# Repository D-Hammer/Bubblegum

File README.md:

# Bubblegum
## Integrated control board

### Scope: 
- Interface with an RC receiver
  - Sbus is priority
  - Other variants will be created later
- Control drive motors
  - 2 motors priority
  - 4 motors later to allow use for Mecanum, etc.
- Control weapon motor
- IMU/PID drive to make up for my lack of driving skill
- Remote adjustable expo, user selectable mixing, sense and remix for inverted driving, remote switch for PID

### To Do
- Test and tune on various drive topologies
- Branch HW and FW to interface w/ standard pwm receivers

# Changelog
## Hardware

### V1.30
- Reduced footprint to 0.94"x0.94"
- Through holes for outputs are now pads to allow for a more compact profile
- 0.8mm FR4, 2oz Cu
- 0.050" pitch programming header

### V1.20
- IMU integrated into control board.  
- 3.3v power system added
- Decreased current capacity on 5V supply to free up board space
- 0.8mm FR4, 2oz Cu

### V1.10
- Increased power input hole diameters

### V1.01
- Rerouted weapon pwm signal to different GPIO
- Added versioning and logo on back silk
- 1.5mm FR4, 1oz Cu

### V1.00
- Prototype
- 0.8mm FR4, 2oz Cu

## Firmware

### 2/6/18
- Minor tweaks to main loop
- Throttle scaling factor added to PID to improve low throttle stability and high throttle tracking
- New boot sequence to communicate with PID tuner
- Library change from SoftwareSerial to NeoSWSerial
- PID Tuner: New, alpha release, programming functions reliably, reading is buggy

### 11/20/17
- Added weapon output to DS branch (servo lib implementation)
- Update PWM branch with DS branch improvements
- New PID gains: P1.8 I0.02 D0.005

### 11/17/17
- Filtered the inversion sensing
- added deadband to PID to stop zero throttle flutter
- PID correction now proportional to throttle input [0.5 + abs(spd)]
- Tuned gains. Settled on P1.2 I0.02 D0.05

### 11/15/17
- Added deadband to drive inputs
- Increased data inclusivity on gyro calibration
- Fixed expo scaling issue
- Fixed sign of gyroOffset in PID
- DShot center is 1048 in 3D mode, NOT 1047 :/

### 11/14/17 
- Added alternate FW for DShot implementation
- dshot fiddlings file uses UART and requires inverter (untested) (DShot150)
- bit banging like an animal is addressable on port D and functional (DShot600)
- New FW syncs ESC update with PID loop and increases frequency from 140 Hz to ~1KHz
- All the standard anti-jitter, digital, checksum goodness you've come to expect from DShot!

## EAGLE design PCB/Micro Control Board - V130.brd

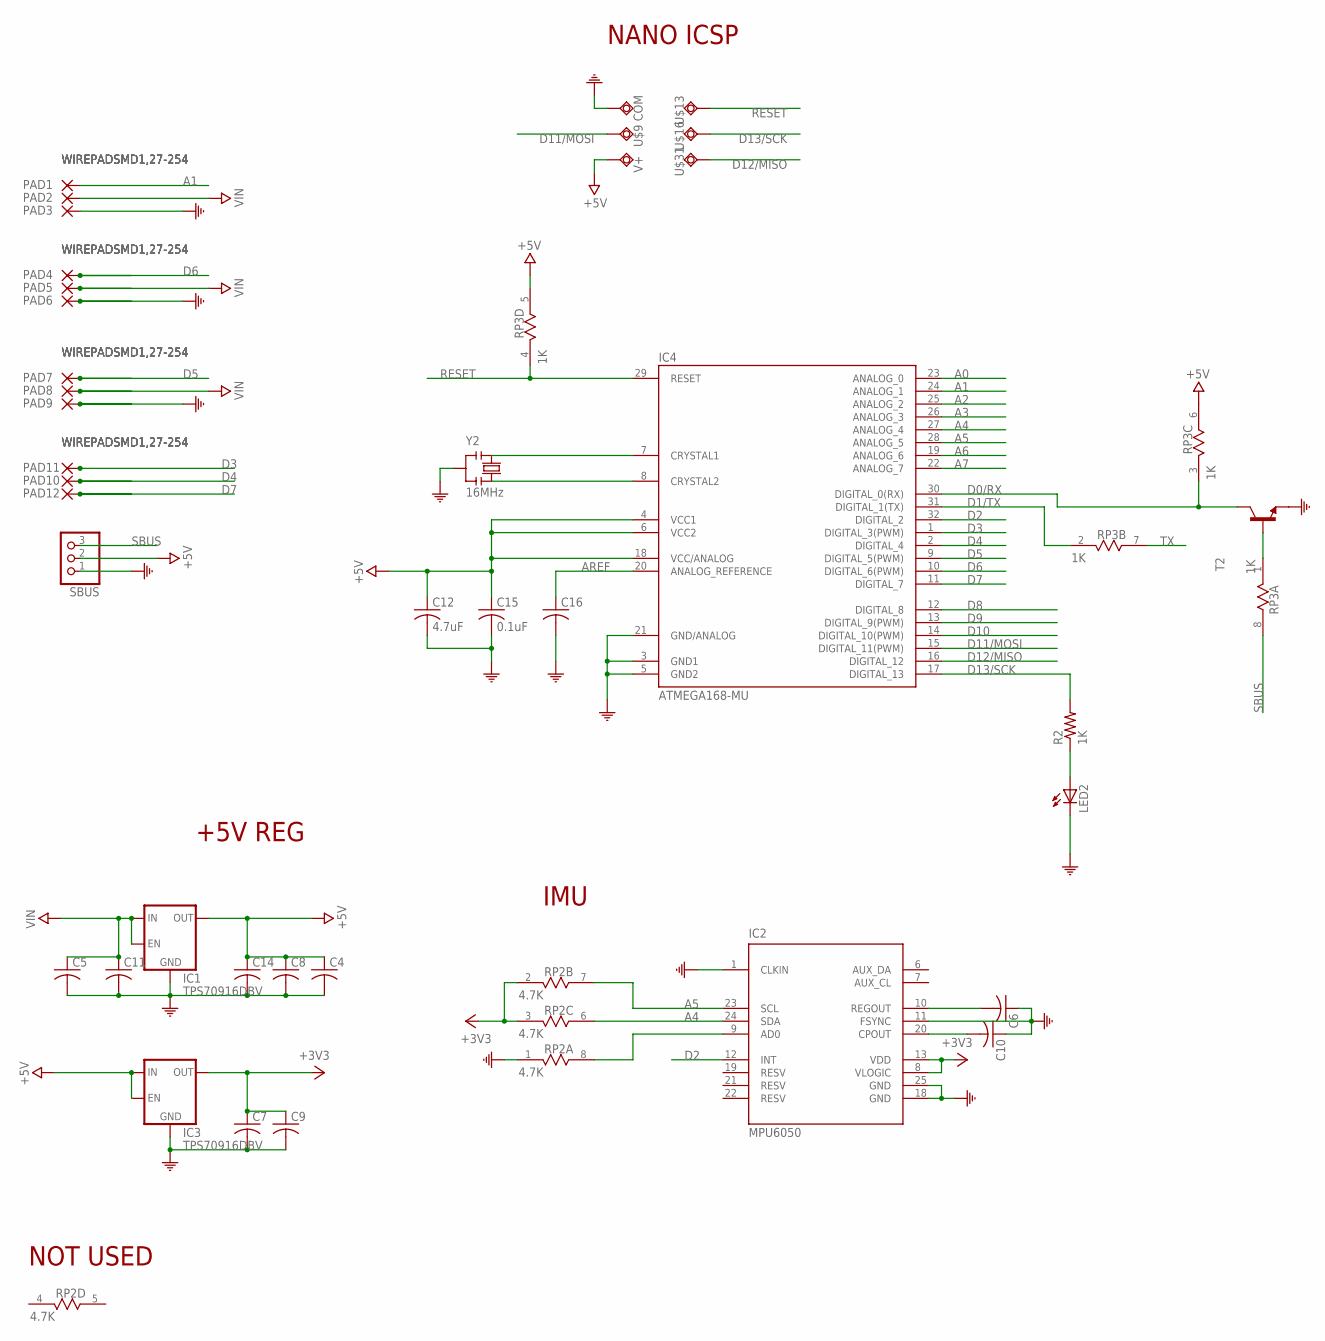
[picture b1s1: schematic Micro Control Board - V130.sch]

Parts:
C4, C5, C6, C7, C8, C9, C10, C11, C14, C16: C-USC0402; C0402
C12: 4.7uF; C0402
C15: 0.1uF; C0402
COM: 0.7MM-THRU; 0.65MM-THRU
IC1, IC3: TPS70916DBV; SOT23-5
IC2: MPU6050; QFN50P400X400X95-25T265X275N
IC4: ATMEGA168-MU; MLF32
LED2: LEDCHIP-LED0603; CHIP-LED0603
PAD1, PAD2, PAD3, PAD4, PAD5, PAD6, PAD7, PAD8, PAD9, PAD10, PAD11, PAD12: WIREPADSMD1,27-254; SMD1,27-2,54
R2: 1K; R0402
RP2: 4.7K; RES4NT
RP3: 1K; RES4NT
SBUS: PINHD-1X3; 1X03
T2: MMBT3904LT1-NPN-SOT23-BEC; SOT23-BEC
U$9, U$13, U$16, U$31: 0.7MM-THRU; 0.65MM-THRU
V+: 0.7MM-THRU; 0.65MM-THRU
Y2: 16MHz; RESONATOR

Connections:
+3V3: C7.1, C9.1, IC2.8 (VLOGIC), IC2.13 (VDD), IC3.5 (OUT), RP2.2 (1), RP2.3 (1)
+5V: C4.1, C8.1, C12.1, C14.1, C15.1, IC1.5 (OUT), IC3.1 (IN), IC3.3 (EN), IC4.4 (VCC1), IC4.6 (VCC2), IC4.18 (VCC/ANALOG), RP3.5 (2), RP3.6 (2), SBUS.2, V+.P$2
A0: IC4.23 (ANALOG_0)
A1: IC4.24 (ANALOG_1), PAD1.1
A2: IC4.25 (ANALOG_2)
A3: IC4.26 (ANALOG_3)
A4: IC2.24 (SDA), IC4.27 (ANALOG_4), RP2.6 (2)
A5: IC2.23 (SCL), IC4.28 (ANALOG_5), RP2.7 (2)
A6: IC4.19 (ANALOG_6)
A7: IC4.22 (ANALOG_7)
AREF: C16.1, IC4.20 (ANALOG_REFERENCE)
COM: C4.2, C5.2, C6.1, C7.2, C8.2, C9.2, C10.1, C11.2, C12.2, C14.2, C15.2, C16.2, COM.P$2, IC1.2 (GND), IC2.1 (CLKIN), IC2.11 (FSYNC), IC2.18 (GND), IC2.25 (GND), IC3.2 (GND), IC4.3 (GND1), IC4.5 (GND2), IC4.21 (GND/ANALOG), LED2.C, PAD3.1, PAD6.1, PAD9.1, RP2.1, SBUS.1, T2.E, Y2.2
D0/RX: IC4.30 (DIGITAL_0(RX)), RP3.3 (1), T2.C
D1/TX: IC4.31 (DIGITAL_1(TX)), RP3.2 (1)
D2: IC2.12 (INT), IC4.32 (DIGITAL_2)
D3: IC4.1 (DIGITAL_3(PWM)), PAD10.1
D4: IC4.2 (DIGITAL_4), PAD11.1
D5: IC4.9 (DIGITAL_5(PWM)), PAD7.1
D6: IC4.10 (DIGITAL_6(PWM)), PAD4.1
D7: IC4.11 (DIGITAL_7), PAD12.1
D8: IC4.12 (DIGITAL_8)
D9: IC4.13 (DIGITAL_9(PWM))
D10: IC4.14 (DIGITAL_10(PWM))
D11/MOSI: IC4.15 (DIGITAL_11(PWM)), U$9.P$2
D12/MISO: IC4.16 (DIGITAL_12), U$31.P$2
D13/SCK: IC4.17 (DIGITAL_13), R2.2, U$16.P$2
unnamed: IC2.9 (AD0), RP2.8 (2)
unnamed: C6.2, IC2.10 (REGOUT)
unnamed: IC4.7 (CRYSTAL1), Y2.1
unnamed: C10.2, IC2.20 (CPOUT)
unnamed: IC4.8 (CRYSTAL2), Y2.3
unnamed: LED2.A, R2.1
unnamed: RP3.1, T2.B
RESET: IC4.29 (RESET), RP3.4 (1), U$13.P$2
SBUS: RP3.8 (2), SBUS.3
TX: RP3.7 (2)
VIN: C5.1, C11.1, IC1.1 (IN), IC1.3 (EN), PAD2.1, PAD5.1, PAD8.1

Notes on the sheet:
+5V REG
NANO ICSP
NOT USED
IMU

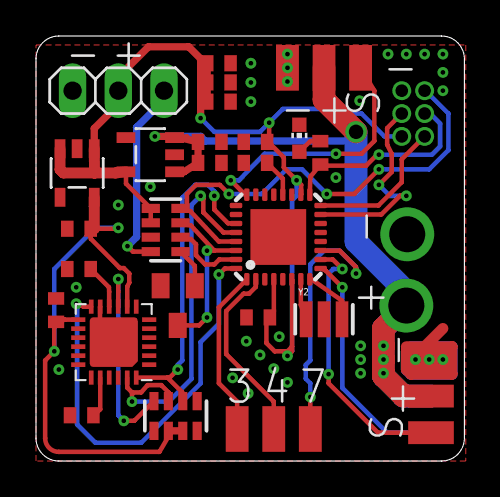
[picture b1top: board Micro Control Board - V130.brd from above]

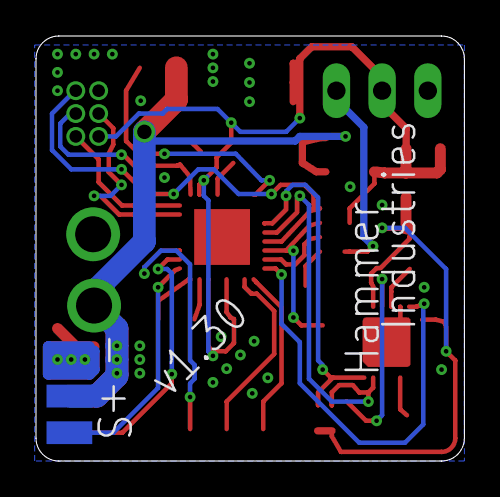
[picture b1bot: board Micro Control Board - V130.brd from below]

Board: 2 copper layers, 23.8 x 23.6 mm, 41 parts (3 on the bottom side), 28 nets.

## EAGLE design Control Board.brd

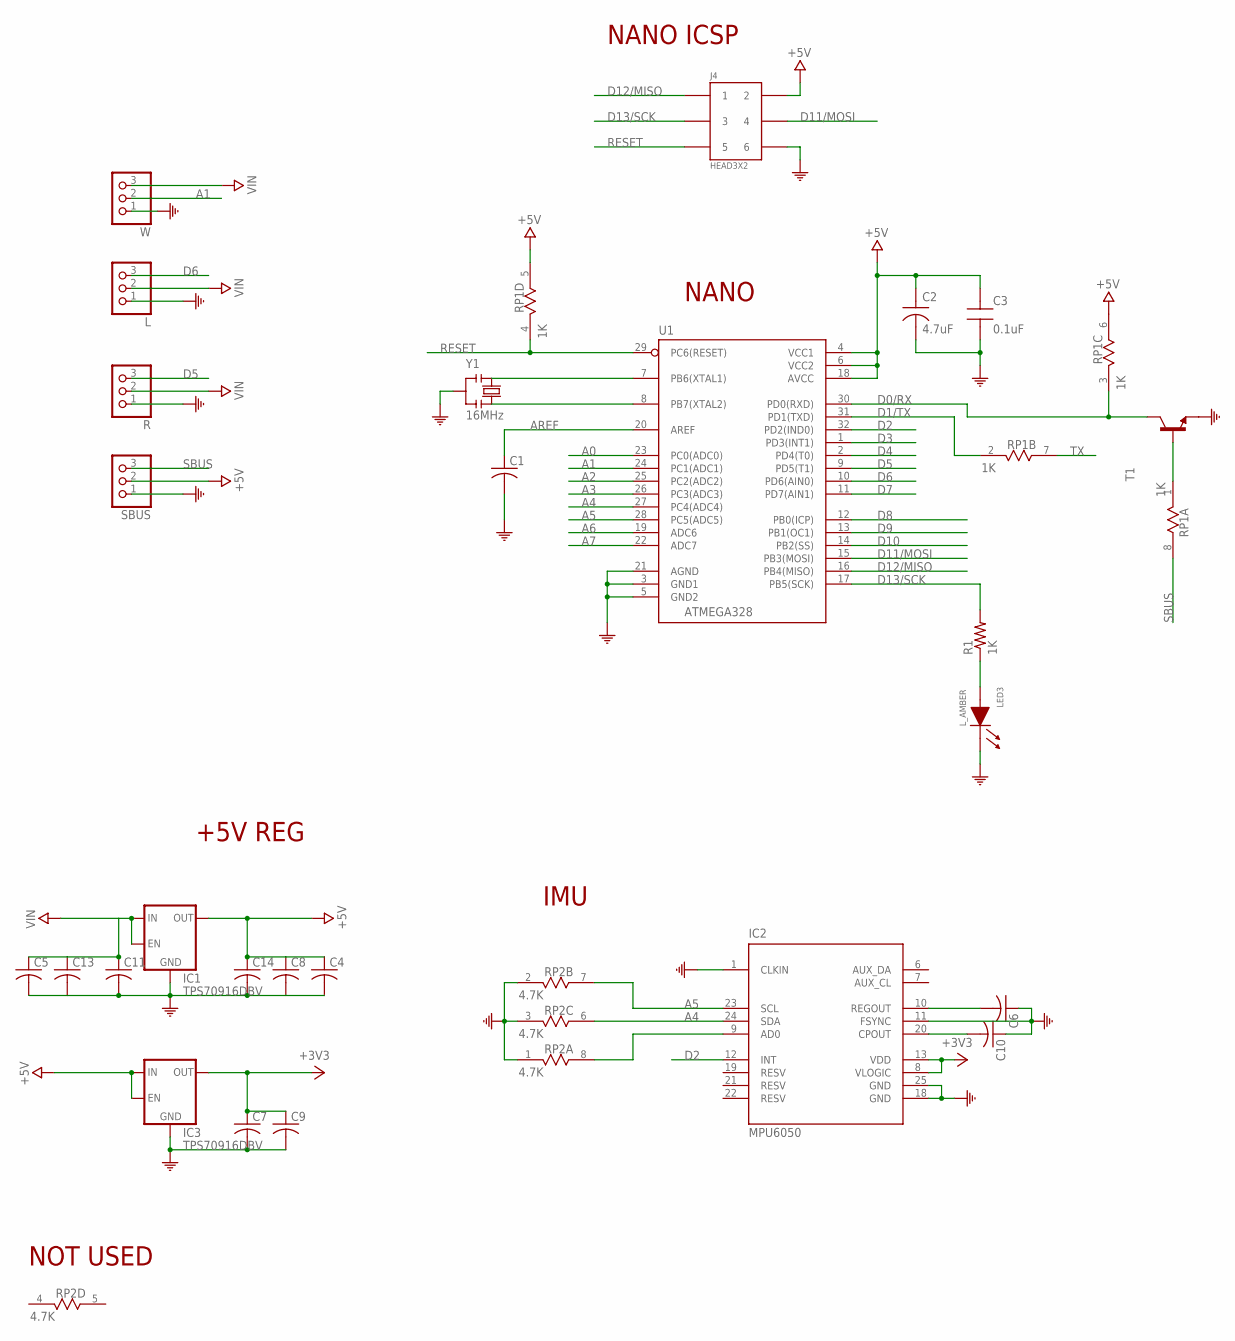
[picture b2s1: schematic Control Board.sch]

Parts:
C1, C4, C5, C6, C7, C8, C9, C10, C11, C13, C14: C-USC0603; C0603
C2: 4.7uF; TAN-A
C3: 0.1uF; CAP0805-NP
IC1, IC3: TPS70916DBV; SOT23-5
IC2: MPU6050; QFN50P400X400X95-25T265X275N
J4: HEAD3X2
L: PINHD-1X3; 1X03
LED3: L_AMBER; LED0805
R: PINHD-1X3; 1X03
R1: 1K; R0603
RP1: 1K; RES4NT
RP2: 4.7K; RES4NT
SBUS: PINHD-1X3; 1X03
T1: MMBT3904LT1-NPN-SOT23-BEC; SOT23-BEC
U1: ATMEGA328; QFP032
W: PINHD-1X3; 1X03
Y1: 16MHz; RESONATOR

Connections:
+3V3: C7.1, C9.1, IC2.8 (VLOGIC), IC2.13 (VDD), IC3.5 (OUT)
+5V: C2.1, C3.1, C4.1, C8.1, C14.1, IC1.5 (OUT), IC3.1 (IN), IC3.3 (EN), J4.2, RP1.5 (2), RP1.6 (2), SBUS.2, U1.4 (VCC1), U1.6 (VCC2), U1.18 (AVCC)
A0: U1.23 (PC0(ADC0))
A1: U1.24 (PC1(ADC1)), W.2
A2: U1.25 (PC2(ADC2))
A3: U1.26 (PC3(ADC3))
A4: IC2.24 (SDA), RP2.6 (2), U1.27 (PC4(ADC4))
A5: IC2.23 (SCL), RP2.7 (2), U1.28 (PC5(ADC5))
A6: U1.19 (ADC6)
A7: U1.22 (ADC7)
AREF: C1.1, U1.20 (AREF)
COM: C1.2, C2.2, C3.2, C4.2, C5.2, C6.1, C7.2, C8.2, C9.2, C10.1, C11.2, C13.2, C14.2, IC1.2 (GND), IC2.1 (CLKIN), IC2.11 (FSYNC), IC2.18 (GND), IC2.25 (GND), IC3.2 (GND), J4.6, L.1, LED3.1 (CA), R.1, RP2.1, RP2.2 (1), RP2.3 (1), SBUS.1, T1.E, U1.3 (GND1), U1.5 (GND2), U1.21 (AGND), W.1, Y1.2
D0/RX: RP1.3 (1), T1.C, U1.30 (PD0(RXD))
D1/TX: RP1.2 (1), U1.31 (PD1(TXD))
D2: IC2.12 (INT), U1.32 (PD2(IND0))
D3: U1.1 (PD3(INT1))
D4: U1.2 (PD4(T0))
D5: R.3, U1.9 (PD5(T1))
D6: L.3, U1.10 (PD6(AIN0))
D7: U1.11 (PD7(AIN1))
D8: U1.12 (PB0(ICP))
D9: U1.13 (PB1(OC1))
D10: U1.14 (PB2(SS))
D11/MOSI: J4.4, U1.15 (PB3(MOSI))
D12/MISO: J4.1, U1.16 (PB4(MISO))
D13/SCK: J4.3, R1.2, U1.17 (PB5(SCK))
unnamed: U1.8 (PB7(XTAL2)), Y1.3
unnamed: U1.7 (PB6(XTAL1)), Y1.1
unnamed: IC2.9 (AD0), RP2.8 (2)
unnamed: C6.2, IC2.10 (REGOUT)
unnamed: RP1.1, T1.B
unnamed: C10.2, IC2.20 (CPOUT)
unnamed: LED3.2 (AN), R1.1
RESET: J4.5, RP1.4 (1), U1.29 (PC6(RESET))
SBUS: RP1.8 (2), SBUS.3
TX: RP1.7 (2)
VIN: C5.1, C11.1, C13.1, IC1.1 (IN), IC1.3 (EN), L.2, R.2, W.3

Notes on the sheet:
NANO
+5V REG
NANO ICSP
NOT USED
IMU

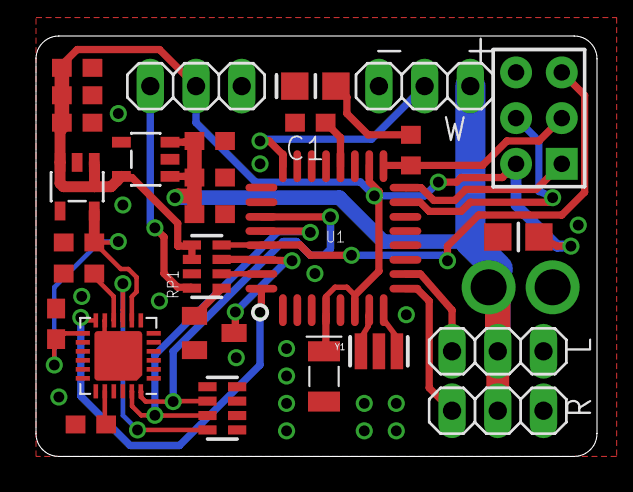
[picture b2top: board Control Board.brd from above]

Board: 2 copper layers, 31.2 x 23.4 mm, 28 parts (0 on the bottom side), 25 nets.

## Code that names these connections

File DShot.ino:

//////////////////////////////////////////////////////////
//////////////////////////////////////////////////////////
// Valid pin values and their corresponding pins:
//  IDE   Port Pin   Value
//  0     PD0       (Don't do it, you're gonna be sad!!!)
//  1     PD1        2
//  2     PD2        4
//  3     PD3        8
//  4     PD4        16
//  5     PD5        32
//  6     PD6        64
//  7     PD7        128
//////////////////////////////////////////////////////////
//////////////////////////////////////////////////////////

void transmit_dShot(int16_t dShotVal, uint8_t pin) {
  // Take in the value from 48 to 2047 (1-47 are reserved) and also the pin location as a binary port map
  DDRD |= pin; // Set the pin as output (just in case...)
  uint8_t checksum = ((dShotVal >> 7)&B1111) ^ ((dShotVal >> 3)&B1111) ^ ((dShotVal << 1)&B1110); // Create the checksum
  dShotVal = (dShotVal << 5) | checksum; // Create the shot frame
  uint8_t notpin = ~pin; // Save clock cycles by doing this now

  // Hundreds of lines of sad ugly bit banging.  It works.  I'm not proud of this
  if ((dShotVal >> 15) & 0x01) { // Check if 1 or 0
    PORTD |= pin;  // Turn the pin on
    PORTD |= pin;  // Waste time
    PORTD |= pin;
    PORTD |= pin;
    PORTD |= pin;
    PORTD &= notpin; //Turn off, then waste more time
    PORTD &= notpin;
  }
  else {
    PORTD |= pin;
    PORTD |= pin;
    PORTD &= notpin;
    PORTD &= notpin;
    PORTD &= notpin;
    PORTD &= notpin;
    PORTD &= notpin;
  }
  if ((dShotVal >> 14) & 0x01) {
    PORTD |= pin;
    PORTD |= pin;
    PORTD |= pin;
    PORTD |= pin;
    PORTD |= pin;
    PORTD |= pin;
    PORTD &= notpin;
    PORTD &= notpin;
  }
  else {
    PORTD |= pin;
    PORTD |= pin;
    PORTD &= notpin;
    PORTD &= notpin;
    PORTD &= notpin;
    PORTD &= notpin;
    PORTD &= notpin;
  }
  if ((dShotVal >> 13) & 0x01) {
    PORTD |= pin;
    PORTD |= pin;
    PORTD |= pin;
    PORTD |= pin;
    PORTD |= pin;
    PORTD |= pin;
    PORTD &= notpin;
    PORTD &= notpin;
  }
  else {
    PORTD |= pin;
    PORTD |= pin;
    PORTD &= notpin;
    PORTD &= notpin;
    PORTD &= notpin;
    PORTD &= notpin;
    PORTD &= notpin;
  }
  if ((dShotVal >> 12) & 0x01) {
    PORTD |= pin;
    PORTD |= pin;
    PORTD |= pin;
    PORTD |= pin;
    PORTD |= pin;
    PORTD |= pin;
    PORTD &= notpin;
    PORTD &= notpin;
  }
  else {
    PORTD |= pin;
    PORTD |= pin;
    PORTD &= notpin;
    PORTD &= notpin;
    PORTD &= notpin;
    PORTD &= notpin;
    PORTD &= notpin;
  }
  if ((dShotVal >> 11) & 0x01) {
    PORTD |= pin;
    PORTD |= pin;
    PORTD |= pin;
    PORTD |= pin;
    PORTD |= pin;
    PORTD |= pin;
    PORTD &= notpin;
    PORTD &= notpin;
  }
  else {
    PORTD |= pin;
    PORTD |= pin;
    PORTD &= notpin;
    PORTD &= notpin;
    PORTD &= notpin;
    PORTD &= notpin;
    PORTD &= notpin;
  }
  if ((dShotVal >> 10) & 0x01) {
    PORTD |= pin;
    PORTD |= pin;
    PORTD |= pin;
    PORTD |= pin;
    PORTD |= pin;
    PORTD |= pin;
    PORTD &= notpin;
    PORTD &= notpin;
  }
  else {
    PORTD |= pin;
    PORTD |= pin;
    PORTD &= notpin;
    PORTD &= notpin;
    PORTD &= notpin;
    PORTD &= notpin;
    PORTD &= notpin;
  }
  if ((dShotVal >> 9) & 0x01) {
    PORTD |= pin;
    PORTD |= pin;
    PORTD |= pin;
    PORTD |= pin;
    PORTD |= pin;
    PORTD |= pin;
    PORTD &= notpin;
    PORTD &= notpin;
  }
  else {
    PORTD |= pin;
    PORTD |= pin;
    PORTD &= notpin;
    PORTD &= notpin;
    PORTD &= notpin;
    PORTD &= notpin;
    PORTD &= notpin;
  }
  if ((dShotVal >> 8) & 0x01) {
    PORTD |= pin;
    PORTD |= pin;
    PORTD |= pin;
    PORTD |= pin;
    PORTD |= pin;
    PORTD |= pin;
    PORTD &= notpin;
    PORTD &= notpin;
  }
  else {
    PORTD |= pin;
    PORTD |= pin;
    PORTD &= notpin;
    PORTD &= notpin;
    PORTD &= notpin;
    PORTD &= notpin;
    PORTD &= notpin;
  }
  if ((dShotVal >> 7) & 0x01) {
    PORTD |= pin;
    PORTD |= pin;
    PORTD |= pin;
    PORTD |= pin;
    PORTD |= pin;
    PORTD |= pin;
    PORTD &= notpin;
    PORTD &= notpin;
  }
  else {
    PORTD |= pin;
    PORTD |= pin;
    PORTD &= notpin;
    PORTD &= notpin;
    PORTD &= notpin;
    PORTD &= notpin;
    PORTD &= notpin;
  }
  if ((dShotVal >> 6) & 0x01) {
    PORTD |= pin;
    PORTD |= pin;
    PORTD |= pin;
    PORTD |= pin;
    PORTD |= pin;
    PORTD |= pin;
    PORTD &= notpin;
    PORTD &= notpin;
  }
  else {
    PORTD |= pin;
    PORTD |= pin;
    PORTD &= notpin;
    PORTD &= notpin;
    PORTD &= notpin;
    PORTD &= notpin;
    PORTD &= notpin;
  }
  if ((dShotVal >> 5) & 0x01) {
    PORTD |= pin;
    PORTD |= pin;
    PORTD |= pin;
    PORTD |= pin;
    PORTD |= pin;
    PORTD |= pin;
    PORTD &= notpin;
    PORTD &= notpin;
  }
  else {
    PORTD |= pin;
    PORTD |= pin;
    PORTD &= notpin;
    PORTD &= notpin;
    PORTD &= notpin;
    PORTD &= notpin;
    PORTD &= notpin;
  }
  if ((dShotVal >> 4) & 0x01) {
    PORTD |= pin;
    PORTD |= pin;
    PORTD |= pin;
    PORTD |= pin;
    PORTD |= pin;
    PORTD |= pin;
    PORTD &= notpin;
    PORTD &= notpin;
  }
  else {
    PORTD |= pin;
    PORTD |= pin;
    PORTD &= notpin;
    PORTD &= notpin;
    PORTD &= notpin;
    PORTD &= notpin;
    PORTD &= notpin;
  }
  if ((dShotVal >> 3) & 0x01) {
    PORTD |= pin;
    PORTD |= pin;
    PORTD |= pin;
    PORTD |= pin;
    PORTD |= pin;
    PORTD |= pin;
    PORTD &= notpin;
    PORTD &= notpin;
  }
  else {
    PORTD |= pin;
    PORTD |= pin;
    PORTD &= notpin;
    PORTD &= notpin;
    PORTD &= notpin;
    PORTD &= notpin;
    PORTD &= notpin;
  }
  if ((dShotVal >> 2) & 0x01) {
    PORTD |= pin;
    PORTD |= pin;
    PORTD |= pin;
    PORTD |= pin;
    PORTD |= pin;
    PORTD |= pin;
    PORTD &= notpin;
    PORTD &= notpin;
  }
  else {
    PORTD |= pin;
    PORTD |= pin;
    PORTD &= notpin;
    PORTD &= notpin;
    PORTD &= notpin;
    PORTD &= notpin;
    PORTD &= notpin;
  }
  if ((dShotVal >> 1) & 0x01) {
    PORTD |= pin;
    PORTD |= pin;
    PORTD |= pin;
    PORTD |= pin;
    PORTD |= pin;
    PORTD |= pin;
    PORTD &= notpin;
    PORTD &= notpin;
  }
  else {
    PORTD |= pin;
    PORTD |= pin;
    PORTD &= notpin;
    PORTD &= notpin;
    PORTD &= notpin;
    PORTD &= notpin;
    PORTD &= notpin;
  }
  if (dShotVal & 0x01) {
    PORTD |= pin;
    PORTD |= pin;
    PORTD |= pin;
    PORTD |= pin;
    PORTD |= pin;
    PORTD |= pin;
    PORTD &= notpin;
    PORTD &= notpin;
  }
  else {
    PORTD |= pin;
    PORTD |= pin;
    PORTD &= notpin;
    PORTD &= notpin;
    PORTD &= notpin;
    PORTD &= notpin;
    PORTD &= notpin;
  }
}

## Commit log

2017-11-20 Rename D_Shot_fiddlings.ino to Research/D_Shot_fiddlings.ino
2017-11-20 Rename Bit_Banging_Like_An_Animal.ino to Research/Bit_Banging_Like_An_Animal.ino
2017-11-20 Rename Control Board.brd to PCB/Control Board.brd
2017-11-20 Rename Control Board.sch to PCB/Control Board.sch
